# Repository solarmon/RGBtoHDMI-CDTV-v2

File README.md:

## Introduction

This is **version 2** of the [RGBtoHDMI CDTV](https://github.com/solarmon/RGBtoHDMI-CDTV) solution.

Improvements over version one are:

* Full sized HDMI port
* DB9 mouse and joystick ports
* JP15 toggle switch

This is an RGBtoHDMI solution is based on the original work by **hoglet67** and **IanSB**:

hoglet67:
https://github.com/hoglet67/RGBtoHDMI

IanSB:
https://github.com/IanSB/RGBtoHDMI

The solution is based on the RGBtoHDMI CPLD based hardware design by **LinuxJedi**:

https://github.com/LinuxJedi/AmigaRGBtoHDMI

Special mention to **c0pperdragon** for the original RGBtoHDMI board solution for the Amiga:

https://github.com/c0pperdragon/Amiga-Digital-Video

## Design Files

The design files are available for **KiCAD v6**.

### RGBtoHDMI CDTV v2 (QFP)

This is the Xilinx XC9572XL QFP 44-pin package version.

This is the main RGBtoHDMI board, with daughter board, and face plate:

[RGBtoHDMI CDTV v2](https://github.com/solarmon/RGBtoHDMI-CDTV-v2/tree/main/RGBtoHDMI%20CDTV%20v2)

Note: Due to limitations of the 3D rendering in KiCAD, some of the colours and components are not accurate.

### RGBtoHDMI CDTV v2 - Denise Breakout

This is the Denise adapter that is required to connect to the main board. It provides the digital RGB video and JP15 signals to the main board.

[RGBtoHDMI CDTV v2 - Denise Breakout](https://github.com/solarmon/RGBtoHDMI-CDTV-v2/tree/main/RGBtoHDMI%20CDTV%20v2%20-%20Denise%20Breakout)

### RGBtoHDMI CDTV v2 - Mouse and Joystick Adapter

This is the mouse and joystick adapter required to connect to the DB9 ports on the main board:

[RGBtoHDMI CDTV v2 - Mouse and Joystick Adapter](https://github.com/solarmon/RGBtoHDMI-CDTV-v2/tree/main/RGBtoHDMI%20CDTV%20v2%20-%20Mouse%20and%20Joystick%20Adapter)

The adapter uses a 18-pin (1mm pitch) FFC flex cable. A 60cm long flex cable is ideally required. However, if only 30cm long flex cables are available then an FFC extender board can be used to join two of them together:

## Wiki

Please see the [wiki](https://github.com/solarmon/RGBtoHDMI-CDTV-v2/wiki) for further details:

[RGBtoHDMI-CDTV-v2-Quick-Start-Guide](https://github.com/solarmon/RGBtoHDMI-CDTV-v2/wiki/RGBtoHDMI-CDTV-v2-Quick-Start-Guide)

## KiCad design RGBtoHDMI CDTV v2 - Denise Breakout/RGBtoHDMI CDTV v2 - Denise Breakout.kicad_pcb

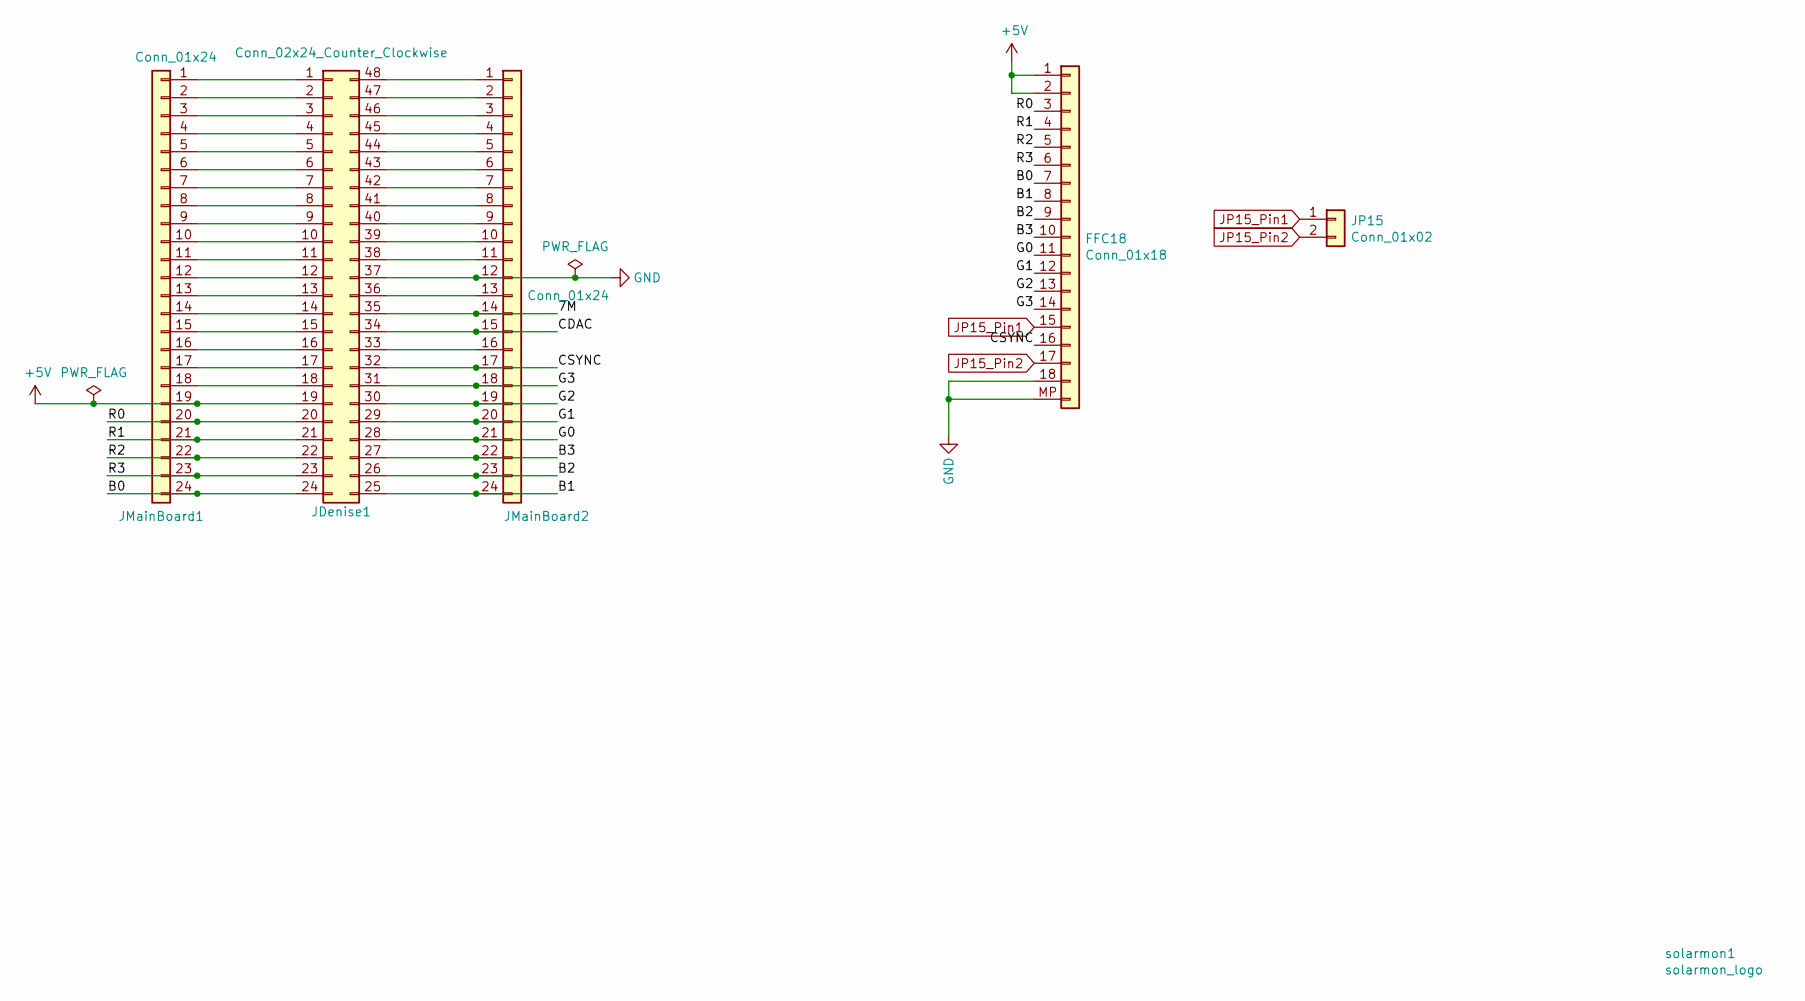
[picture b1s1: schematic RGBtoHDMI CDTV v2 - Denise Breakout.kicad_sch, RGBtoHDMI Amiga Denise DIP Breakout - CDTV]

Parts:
FFC18: Conn_01x18; FPC-SMD_X10B25U18T
JDenise1: Conn_02x24_Counter_Clockwise; DIP-48_W15.24mm_LongPads
JMainBoard1, JMainBoard2: Conn_01x24; PinHeader_1x24_P2.54mm_Vertical_smaller
JP15: Conn_01x02; PinHeader_1x02_P2.54mm_Horizontal
solarmon1: solarmon_logo; solarmon-logo-25mils

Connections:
+5V: FFC18.1, FFC18.2, JDenise1.19, JMainBoard1.19
/7M: JDenise1.35, JMainBoard2.14
/B0: FFC18.7, JDenise1.24, JMainBoard1.24
/B1: FFC18.8, JDenise1.25, JMainBoard2.24
/B2: FFC18.9, JDenise1.26, JMainBoard2.23
/B3: FFC18.10, JDenise1.27, JMainBoard2.22
/CDAC: JDenise1.34, JMainBoard2.15
/CSYNC: FFC18.16, JDenise1.32, JMainBoard2.17
/G0: FFC18.11, JDenise1.28, JMainBoard2.21
/G1: FFC18.12, JDenise1.29, JMainBoard2.20
/G2: FFC18.13, JDenise1.30, JMainBoard2.19
/G3: FFC18.14, JDenise1.31, JMainBoard2.18
/R0: FFC18.3, JDenise1.20, JMainBoard1.20
/R1: FFC18.4, JDenise1.21, JMainBoard1.21
/R2: FFC18.5, JDenise1.22, JMainBoard1.22
/R3: FFC18.6, JDenise1.23, JMainBoard1.23
GND: FFC18.18, FFC18.MP, JDenise1.37, JMainBoard2.12
JP15_Pin1: FFC18.15, JP15.1
JP15_Pin2: FFC18.17, JP15.2
unnamed: JDenise1.1, JMainBoard1.1
unnamed: JDenise1.2, JMainBoard1.2
unnamed: JDenise1.3, JMainBoard1.3
unnamed: JDenise1.4, JMainBoard1.4
unnamed: JDenise1.5, JMainBoard1.5
unnamed: JDenise1.6, JMainBoard1.6
unnamed: JDenise1.7, JMainBoard1.7
unnamed: JDenise1.8, JMainBoard1.8
unnamed: JDenise1.9, JMainBoard1.9
unnamed: JDenise1.10, JMainBoard1.10
unnamed: JDenise1.11, JMainBoard1.11
unnamed: JDenise1.12, JMainBoard1.12
unnamed: JDenise1.13, JMainBoard1.13
unnamed: JDenise1.14, JMainBoard1.14
unnamed: JDenise1.15, JMainBoard1.15
unnamed: JDenise1.16, JMainBoard1.16
unnamed: JDenise1.17, JMainBoard1.17
unnamed: JDenise1.18, JMainBoard1.18
unnamed: JDenise1.33, JMainBoard2.16
unnamed: JDenise1.36, JMainBoard2.13
unnamed: JDenise1.38, JMainBoard2.11
unnamed: JDenise1.39, JMainBoard2.10
unnamed: JDenise1.40, JMainBoard2.9
unnamed: JDenise1.41, JMainBoard2.8
unnamed: JDenise1.42, JMainBoard2.7
unnamed: JDenise1.43, JMainBoard2.6
unnamed: JDenise1.44, JMainBoard2.5
unnamed: JDenise1.45, JMainBoard2.4
unnamed: JDenise1.46, JMainBoard2.3
unnamed: JDenise1.47, JMainBoard2.2
unnamed: JDenise1.48, JMainBoard2.1

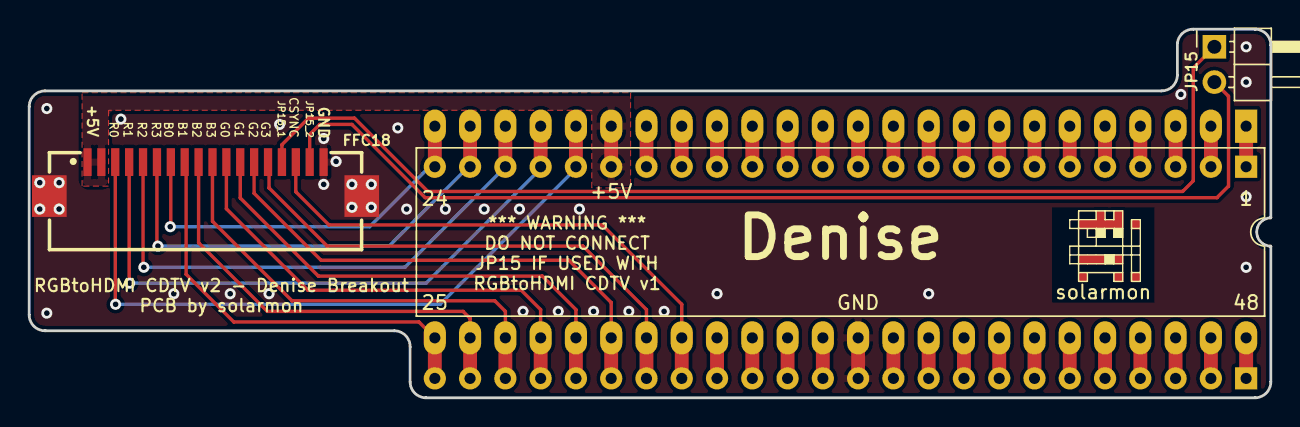
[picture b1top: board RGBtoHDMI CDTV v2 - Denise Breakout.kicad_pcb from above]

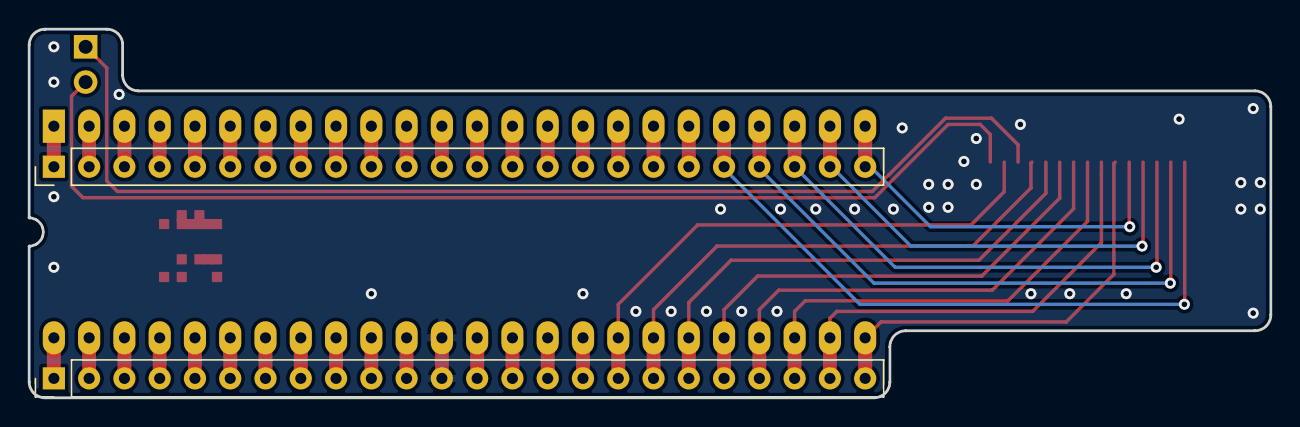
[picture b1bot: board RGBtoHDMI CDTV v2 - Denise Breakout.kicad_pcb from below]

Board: 2 copper layers, 89.4 x 26.5 mm, 6 parts (2 on the bottom side), 50 nets.

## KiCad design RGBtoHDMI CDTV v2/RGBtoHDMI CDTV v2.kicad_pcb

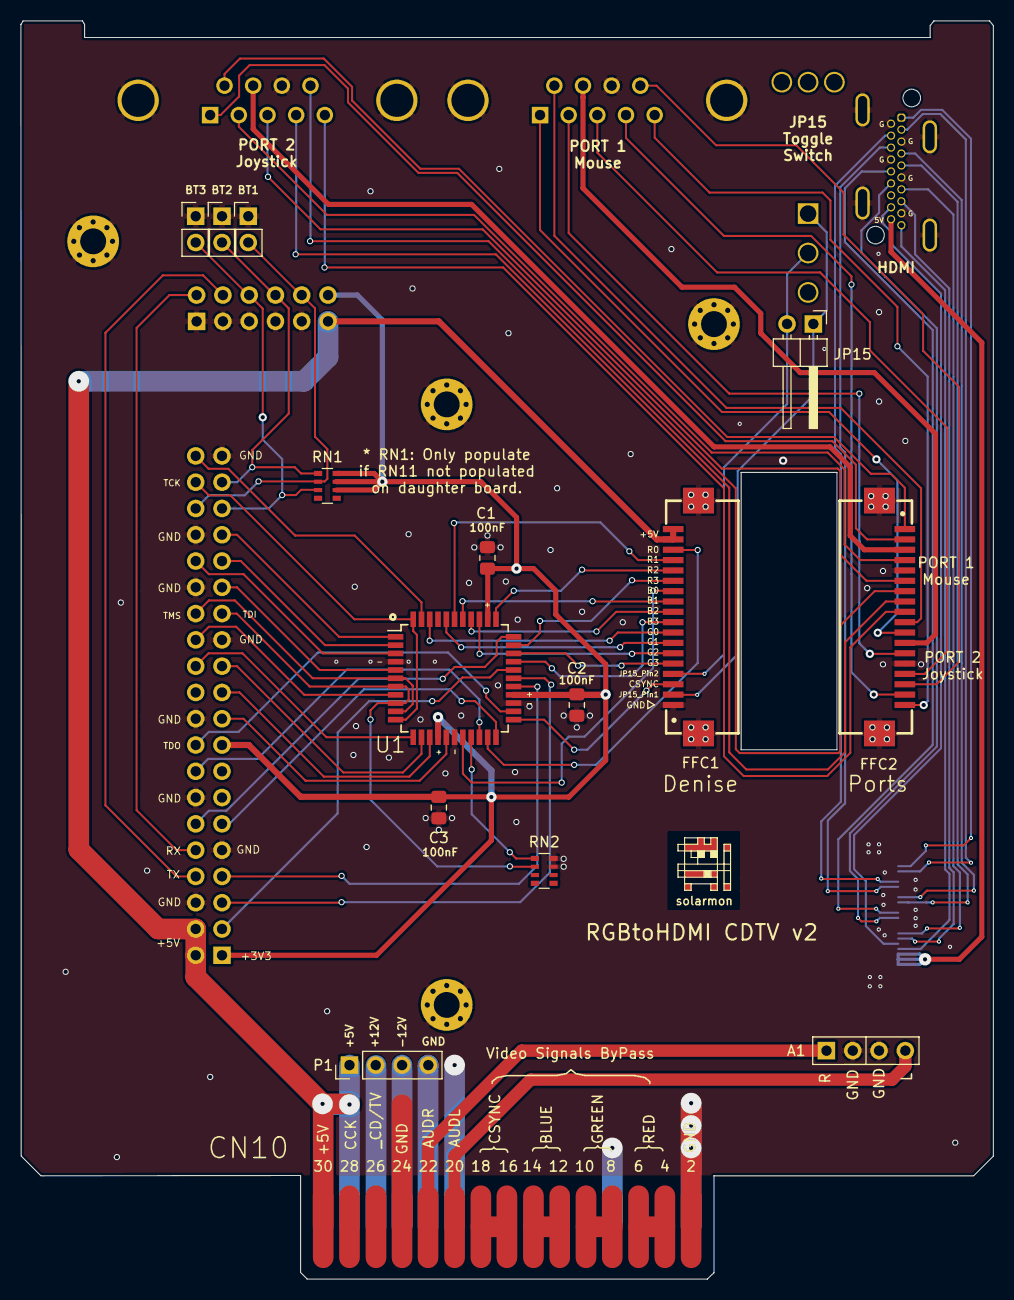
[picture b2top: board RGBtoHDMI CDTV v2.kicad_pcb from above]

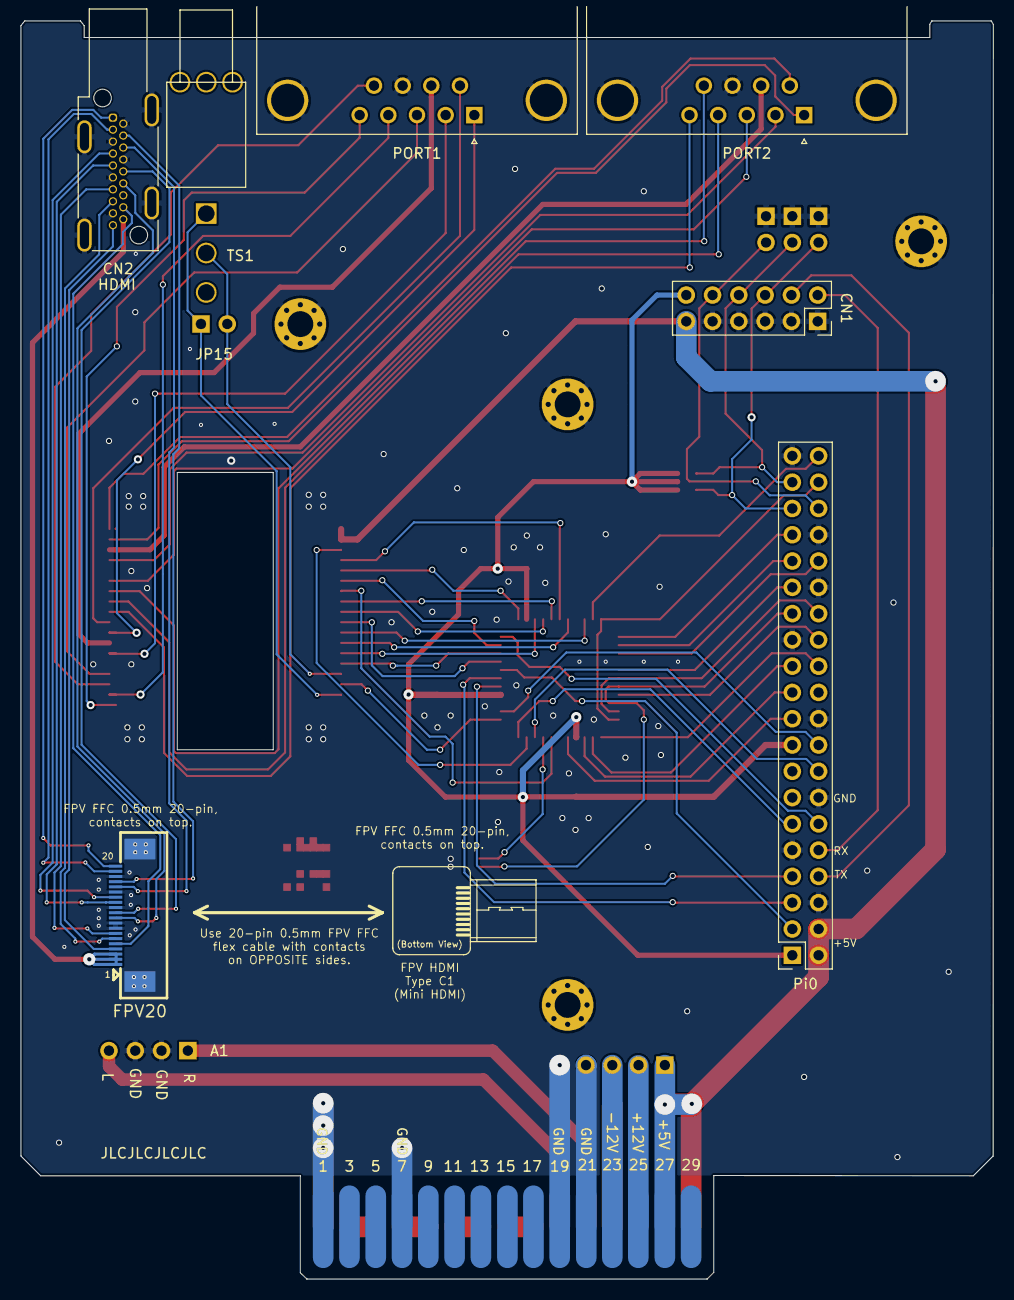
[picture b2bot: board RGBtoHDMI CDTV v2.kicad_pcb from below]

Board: 2 copper layers, 94.0 x 121.6 mm, 27 parts (7 on the bottom side), 81 nets.

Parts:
A1: Conn_01x04; PinHeader_1x04_P2.54mm_Vertical
BT1, BT2, BT3: Jumper_2_Open; PinHeader_1x02_P2.54mm_Vertical
C1, C2, C3: 100nF; C_0805_2012Metric_Pad1.18x1.45mm_HandSolder
CN1: Conn_02x06_Odd_Even; PinSocket_2x06_P2.54mm_Vertical
CN2: HDMI_A; HDMI_A_Kycon_KDMIX-SL1-NS-WS-B15_VerticalRightAngle
CN10: Conn_02x15_Odd_Even; CDTV_Video_Slot_30_pin
FFC1, FFC2: Conn_01x18; FPC-SMD_X10B25U18T
FPV20: Conn_01x20; XFCN_F0501-T-20-20T-R
H1, H2, H3, H4: MountingHole_Pad; MountingHole_2.5mm_Pad_Via
JP15: Conn_01x02; PinHeader_1x02_P2.54mm_Horizontal
P1: Conn_01x04; PinHeader_1x04_P2.54mm_Vertical
PORT1, PORT2: DB9_Male_MountingHoles; DSUB-9_Male_Horizontal_P2.77x2.84mm_EdgePinOffset7.70mm_Hou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
Pi0: Raspberry_Pi_2_3; PinSocket_2x20_P2.54mm_Vertical
RN1, RN2: 4K7; R_Array_Convex_4x0603
TS1: SW_SPDT; T8019L_T8020LB
U1: XC9572XL-10VQ44C or XC9572XL-10VQG44C; TQFP-44_10x10mm_P0.8mm
solarmon1: solarmon_logo; solarmon-logo-25mils

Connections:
+3V3: C1.1, C2.1, C3.1, CN1.12, Pi0.1, Pi0.17, RN1.6, RN1.7, RN1.8, U1.15, U1.26, U1.35
+5V: CN1.11, CN10.27, CN10.30, FFC1.17, FFC1.18, P1.1, Pi0.2, Pi0.4
+12V: CN10.25, P1.2
-12V: CN10.23, P1.3
/B0: FFC1.12, U1.18
/B1: FFC1.11, U1.38
/B2: FFC1.10, U1.37
/B3: FFC1.9, U1.30
/CLKEN: Pi0.28, U1.6, U1.10
/CSYNC: FFC1.3, U1.23
/DETECT: RN2.1, U1.19
/G0: FFC1.8, U1.42
/G1: FFC1.7, U1.40
/G2: FFC1.6, U1.36
/G3: FFC1.5, U1.31
/GPIO0: Pi0.27, RN2.2, U1.7, U1.9
/GPIO2: Pi0.3, U1.29
/GPIO3: Pi0.5, U1.28
/GPIO4: Pi0.7, U1.27
/GPIO5: Pi0.29, U1.5
/GPIO6: Pi0.31, U1.2
/GPIO7: Pi0.26, U1.8
/GPIO8: Pi0.24, U1.12
/GPIO9: Pi0.21, U1.14
/GPIO10: Pi0.19, U1.16
/GPIO11: Pi0.23, U1.13
/GPIO12: Pi0.32, U1.3
/GPIO13: Pi0.33, U1.1
/GPIO14: CN1.4, Pi0.8
/GPIO15: CN1.2, Pi0.10
/GPIO16: BT1.2, CN1.10, Pi0.36, RN1.2
/GPIO17: Pi0.11, U1.22
/GPIO18: Pi0.12, U1.33
/GPIO19: BT3.2, CN1.6, Pi0.35, RN1.3
/GPIO20: Pi0.38, U1.11, U1.44
/GPIO21: Pi0.40, U1.43
/GPIO23: Pi0.16, U1.20
/GPIO24: Pi0.18, U1.24
/GPIO26: BT2.2, CN1.8, Pi0.37, RN1.1
/R0: FFC1.16, U1.21
/R1: FFC1.15, U1.39
/R2: FFC1.14, U1.34
/R3: FFC1.13, U1.32
AB: CN10.12, CN10.14
AC: CN10.16, CN10.18
AG: CN10.8, CN10.10
AR: CN10.4, CN10.6
AUDL: A1.4, CN10.20
AUDR: A1.1, CN10.22
GND: A1.2, A1.3, BT1.1, BT2.1, BT3.1, C1.2, C2.2, C3.2, CN1.1, CN1.3, CN1.5, CN1.7, CN1.9, CN2.2, CN2.5, CN2.8, CN2.11, CN2.17, CN2.SH, CN10.1, CN10.2, CN10.7, CN10.19, CN10.21, CN10.24, FFC1.1, FFC1.MP, FFC2.5, FFC2.14, FFC2.MP, FPV20.8, FPV20.9, FPV20.12, FPV20.15, FPV20.18, FPV20.MP, H1.1, H2.1, H3.1, H4.1, P1.4, PORT1.0, PORT1.8, PORT2.0, PORT2.8, Pi0.6, Pi0.9, Pi0.14, Pi0.20, Pi0.25, Pi0.30, Pi0.34, Pi0.39, RN2.7, RN2.8, U1.4, U1.17, U1.25
HDMI_1_D2+: CN2.1, FPV20.20
HDMI_3_D2-: CN2.3, FPV20.19
HDMI_4_D1+: CN2.4, FPV20.17
HDMI_5V: CN2.18, FPV20.1, FPV20.2, FPV20.3
HDMI_6_D1-: CN2.6, FPV20.16
HDMI_7_D0+: CN2.7, FPV20.14
HDMI_9_D0-: CN2.9, FPV20.13
HDMI_10_CK+: CN2.10, FPV20.11
HDMI_12_CK-: CN2.12, FPV20.10
HDMI_13_CEC: CN2.13, FPV20.7
HDMI_15_SCL: CN2.15, FPV20.6
HDMI_16_SDA: CN2.16, FPV20.5
HDMI_19_HPD: CN2.19, FPV20.4
JP15_Pin1: FFC1.2, JP15.1, TS1.1
JP15_Pin2: FFC1.4, JP15.2, TS1.2
Port1_1: FFC2.11, PORT1.1
Port1_2: FFC2.13, PORT1.2
Port1_3: FFC2.15, PORT1.3
Port1_4: FFC2.17, PORT1.4
Port1_5: FFC2.18, PORT1.5
Port1_6: FFC2.10, PORT1.6
Port1_7: FFC2.12, PORT1.7
Port1_9: FFC2.16, PORT1.9
Port2_1: FFC2.2, PORT2.1
Port2_2: FFC2.4, PORT2.2
Port2_3: FFC2.6, PORT2.3
Port2_4: FFC2.8, PORT2.4
Port2_5: FFC2.9, PORT2.5
Port2_6: FFC2.1, PORT2.6
Port2_7: FFC2.3, PORT2.7
Port2_9: FFC2.7, PORT2.9

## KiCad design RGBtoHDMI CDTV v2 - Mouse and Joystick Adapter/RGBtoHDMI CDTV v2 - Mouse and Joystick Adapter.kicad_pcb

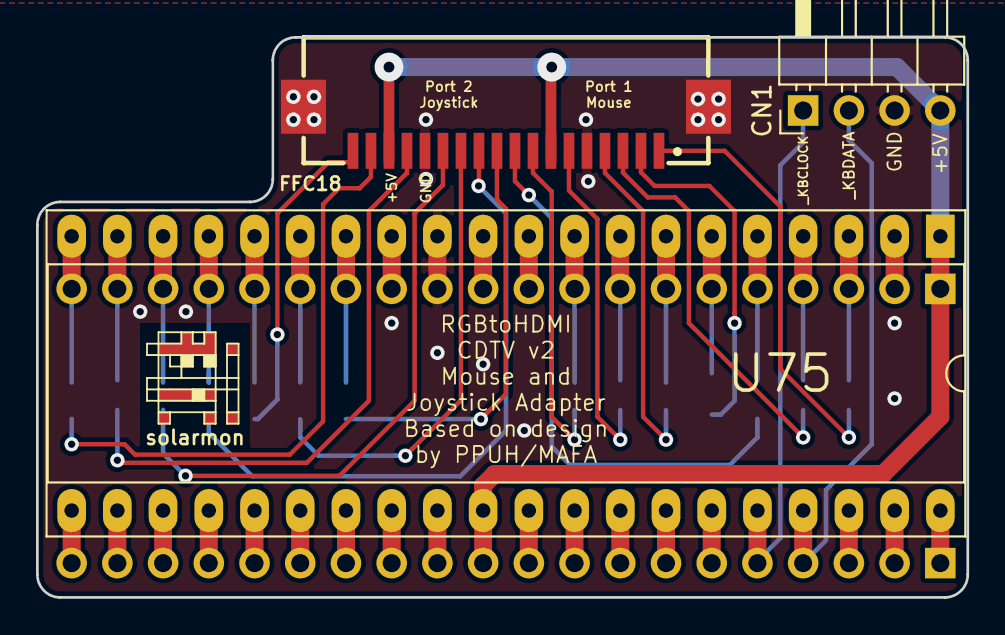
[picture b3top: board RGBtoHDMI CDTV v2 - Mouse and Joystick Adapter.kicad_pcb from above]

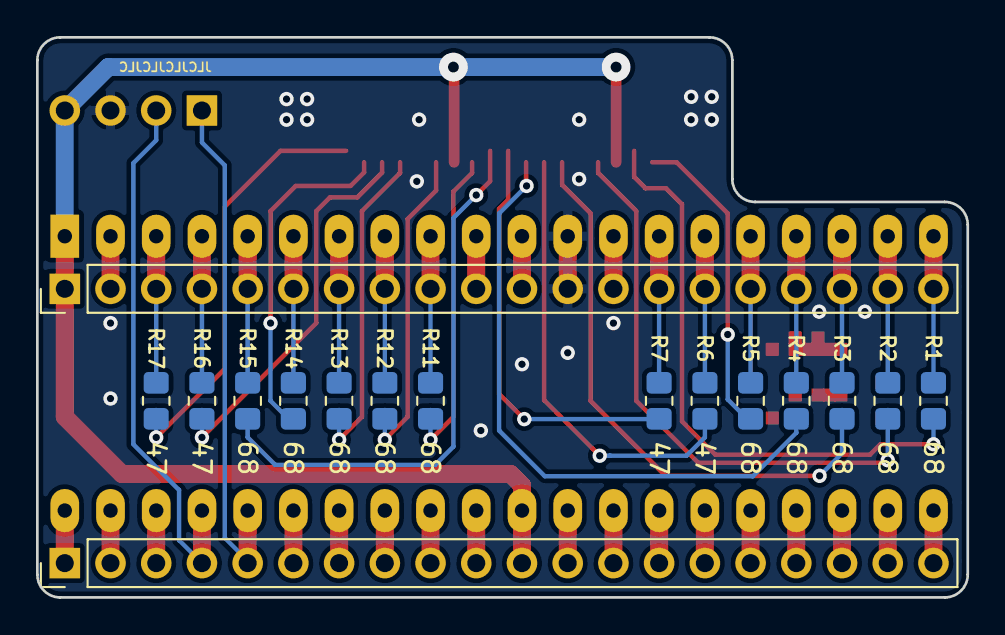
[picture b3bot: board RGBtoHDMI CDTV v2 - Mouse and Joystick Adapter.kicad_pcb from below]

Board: 2 copper layers, 51.7 x 31.1 mm, 20 parts (16 on the bottom side), 53 nets.

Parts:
CN1: Conn_01x04; PinHeader_1x04_P2.54mm_Horizontal
FFC18: FFC_18; FPC-SMD_X10B25U18T
J1, J2: Conn_01x20; PinHeader_1x20_P2.54mm_Vertical
R1, R2, R3, R4, R5, R11, R12, R13, R14, R15: 68; R_0805_2012Metric_Pad1.20x1.40mm_HandSolder
R6, R7, R16, R17: 47; R_0805_2012Metric_Pad1.20x1.40mm_HandSolder
U75: Conn_02x20_Counter_Clockwise; DIP-40_W15.24mm_Socket_LongPads
solarmon1: solarmon_logo; solarmon-logo-25mils

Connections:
+5V: CN1.4, FFC18.7, FFC18.16, J1.1, J2.11, U75.1, U75.30
GND: CN1.3, FFC18.5, FFC18.14, FFC18.MP, J1.12, U75.12
unnamed: J1.2, U75.2
unnamed: J1.3, R17.2, U75.3
unnamed: J1.4, R16.2, U75.4
unnamed: J1.5, R15.2, U75.5
unnamed: J1.6, R14.2, U75.6
unnamed: J1.7, R13.2, U75.7
unnamed: J1.8, R12.2, U75.8
unnamed: J1.9, R11.2, U75.9
unnamed: J1.10, U75.10
unnamed: J1.11, U75.11
unnamed: J1.13, U75.13
unnamed: J1.14, R7.2, U75.14
unnamed: J1.15, R6.2, U75.15
unnamed: J1.16, R5.2, U75.16
unnamed: J1.17, R4.2, U75.17
unnamed: J1.18, R3.2, U75.18
unnamed: J1.19, R2.2, U75.19
unnamed: J1.20, R1.2, U75.20
unnamed: J2.1, U75.40
unnamed: J2.2, U75.39
unnamed: J2.3, U75.38
unnamed: J2.6, U75.35
unnamed: J2.7, U75.34
unnamed: J2.8, U75.33
unnamed: J2.9, U75.32
unnamed: J2.10, U75.31
unnamed: J2.12, U75.29
unnamed: J2.13, U75.28
unnamed: J2.14, U75.27
unnamed: J2.15, U75.26
unnamed: J2.16, U75.25
unnamed: J2.17, U75.24
unnamed: J2.18, U75.23
unnamed: J2.19, U75.22
unnamed: J2.20, U75.21
Port1_1_YB1: FFC18.8, R11.1
Port1_2_XA1: FFC18.6, R12.1
Port1_3_YA1: FFC18.4, R13.1
Port1_4_XB1: FFC18.2, R14.1
Port1_5_POT0X: FFC18.1, R17.1
Port1_6_FIRE0: FFC18.9, R15.1
Port1_9_POT0Y: FFC18.3, R16.1
Port2_1_YB2: FFC18.17, R1.1
Port2_2_XA2: FFC18.15, R2.1
Port2_3_YA2: FFC18.13, R3.1
Port2_4_XB2: FFC18.11, R4.1
Port2_5_POT1X: FFC18.10, R7.1
Port2_6_FIRE1: FFC18.18, R5.1
Port2_9_POT1Y: FFC18.12, R6.1
_KBCLOCK: CN1.1, J2.5, U75.36
_KBDATA: CN1.2, J2.4, U75.37

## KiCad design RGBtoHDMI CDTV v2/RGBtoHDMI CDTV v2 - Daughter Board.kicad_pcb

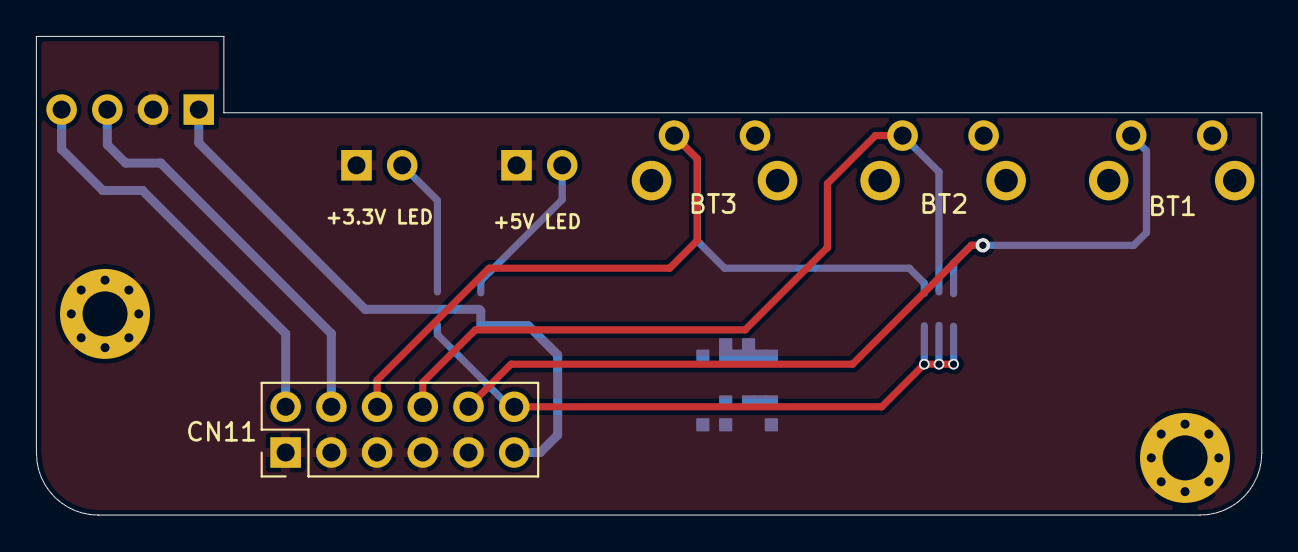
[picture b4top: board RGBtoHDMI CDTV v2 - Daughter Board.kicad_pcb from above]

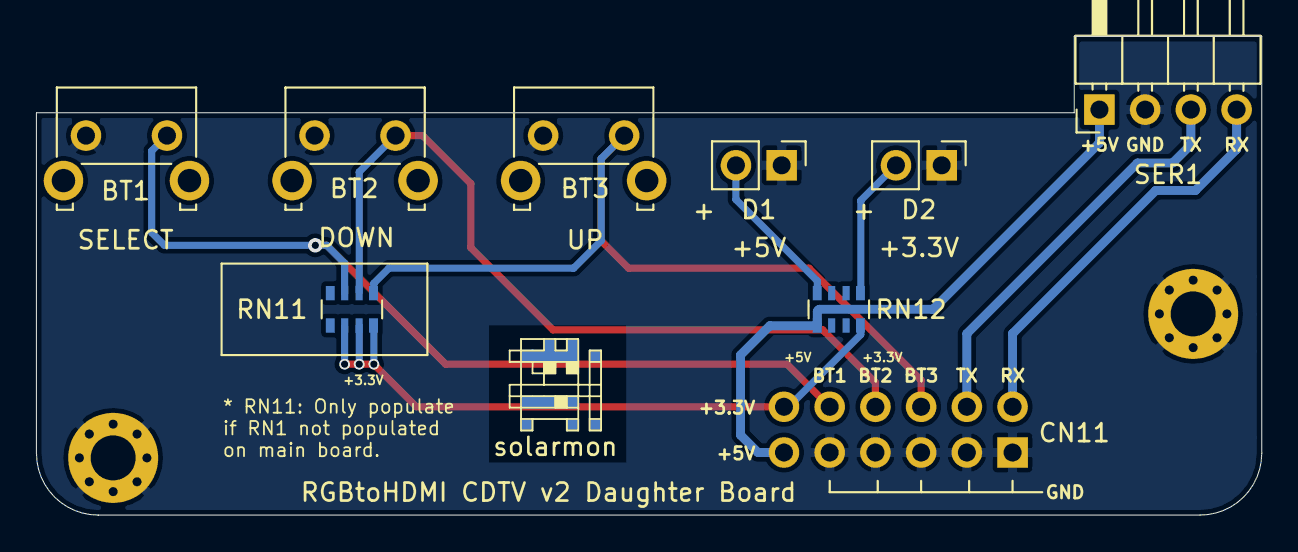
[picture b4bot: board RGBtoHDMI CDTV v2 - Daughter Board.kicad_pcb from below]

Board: 2 copper layers, 68.1 x 26.6 mm, 12 parts (9 on the bottom side), 10 nets.

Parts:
BT1, BT2, BT3: SW_Push; SW_Tactile_SKHH_Angled
CN11: Conn_02x06_Odd_Even; PinHeader_2x06_P2.54mm_Vertical
D1, D2: LED; PinHeader_1x02_P2.54mm_Vertical
H1, H2: MountingHole_Pad; MountingHole_2.5mm_Pad_Via
RN11, RN12: 4K7; R_Array_Convex_4x0603
SER1: Conn_01x04; PinHeader_1x04_P2.54mm_Horizontal
solarmon1: solarmon_logo; solarmon-logo-25mils

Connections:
+3V3: CN11.12, RN11.6, RN11.7, RN11.8, RN12.4
+5V: CN11.11, RN12.1, SER1.1
GND: BT1.1, BT2.1, BT3.1, CN11.1, CN11.3, CN11.5, CN11.7, CN11.9, D1.1, D2.1, H1.1, H2.1, SER1.2
GPIO14: CN11.4, SER1.3
GPIO15: CN11.2, SER1.4
GPIO16: BT1.2, CN11.10, RN11.3
GPIO19: BT3.2, CN11.6, RN11.1
GPIO26: BT2.2, CN11.8, RN11.2
unnamed: D1.2, RN12.8
unnamed: D2.2, RN12.5

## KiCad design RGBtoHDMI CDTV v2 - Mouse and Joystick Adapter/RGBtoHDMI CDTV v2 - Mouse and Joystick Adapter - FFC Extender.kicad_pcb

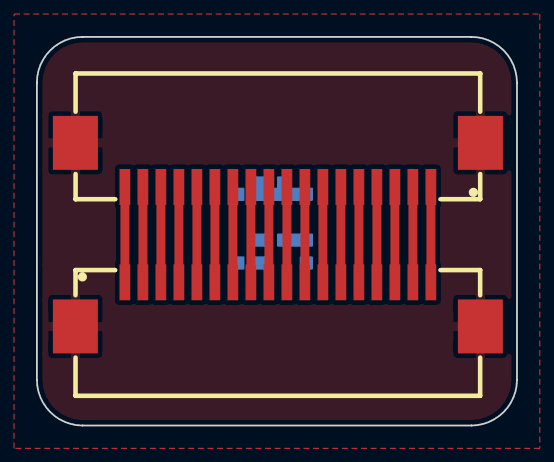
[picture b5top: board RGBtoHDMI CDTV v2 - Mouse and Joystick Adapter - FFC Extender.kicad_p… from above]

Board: 2 copper layers, 26.7 x 21.6 mm, 3 parts (1 on the bottom side), 19 nets.

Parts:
FFC1, FFC2: FFC_18; FPC-SMD_X10B25U18T
solarmon1: solarmon_logo; solarmon-logo-25mils

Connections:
GND: FFC1.MP, FFC2.MP
unnamed: FFC1.1, FFC2.18
unnamed: FFC1.2, FFC2.17
unnamed: FFC1.3, FFC2.16
unnamed: FFC1.4, FFC2.15
unnamed: FFC1.5, FFC2.14
unnamed: FFC1.6, FFC2.13
unnamed: FFC1.7, FFC2.12
unnamed: FFC1.8, FFC2.11
unnamed: FFC1.9, FFC2.10
unnamed: FFC1.10, FFC2.9
unnamed: FFC1.11, FFC2.8
unnamed: FFC1.12, FFC2.7
unnamed: FFC1.13, FFC2.6
unnamed: FFC1.14, FFC2.5
unnamed: FFC1.15, FFC2.4
unnamed: FFC1.16, FFC2.3
unnamed: FFC1.17, FFC2.2
unnamed: FFC1.18, FFC2.1

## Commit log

2022-04-06 Added installation pictures
2022-04-06 Renamed FFC to FPV
2022-04-06 Annotated flex cables
2022-10-09 Uploaded design files
    Uploaded design files for:
    * RGBtoHDMI CDTV v2
    * RGBtoHDMI CDTV v2 - Denise Breakout
    * RGBtoHDMI CDTV v2 - Mouse and Joystick Adapter
2022-10-09 Updated pictures
2022-10-09 Added fully assembled pictures
2022-10-10 Convert daughterboard schematic to KiCAD v6
2022-10-10 Added FFC Extender picture
